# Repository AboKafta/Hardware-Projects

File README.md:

# Hardware Projects

My engineering work, split into personal projects and school projects, each in its own folder.

## Personal Projects

### PCB

| Project | Tool | Description |
|---|---|---|
| [RP2350 Dev Board](Personal/PCB/RP2350-Dev-Board) | KiCad | Custom development board for the RP2350 microcontroller, with bring-up and GPIO test firmware |
| [Room Temperature Monitor](Personal/PCB/Room-Temperature-Monitor) | Altium | Room temperature monitor on a custom PCB built around an Arduino Nano |
| [Piano](Personal/PCB/Piano) | KiCad | Arduino Nano-based piano board with a piezo speaker |
| [Blinking Heart](Personal/PCB/BlinkingHeart) | KiCad | Battery-powered blinking LED heart board |

### Embedded

| Project | Tool | Description |
|---|---|---|
| [MP3 Player](Personal/Embedded/MP3-Player) | Arduino | MP3 player firmware with a wiring diagram |
| [Prosthetic Hand](Personal/Embedded/ProstheticHand) (unfinished) | Arduino | Prototype firmware driving motors from sensor input |

## School Projects

| Project | Course | Tools | Description |
|---|---|---|---|
| [Escape Room Watch](School/Escape-Room-Watch) | Cornerstone of Engineering 2 | Arduino, SolidWorks | Team project: a space-themed escape room puzzle. An Arduino Nano plays three songs on a buzzer, and guessing all three with the buttons shows a lock code on an OLED. I built the electronics and wrote the firmware; my teammates designed and 3D-printed the watch and transmitter (models in `CAD`) |
| [Frog Launcher](School/Frog-Launcher) | Cornerstone of Engineering 1 | MicroPython | Team project: an arcade machine where players launch frogs onto lily pads worth 1 to 3 points and avoid alligators worth -1. I wrote all the code for the Raspberry Pi Pico, built the LCD scoreboard, and rewired the circuit |
| [Chessboard](School/Chessboard) | Cornerstone of Engineering 2 | SolidWorks | Kingdom Hearts-themed chess set: the board and every piece modeled as parts and an assembly, with a final report |
| [Secrets of the Phoenicians](School/Secrets-of-the-Phoenicians) | Cornerstone of Engineering 2 | MATLAB App Designer | Puzzle adventure game set in ancient Phoenicia, using switches, a dropdown, and buttons, with three endings |
| [RPG Fighting Game](School/RPG-Fighting-Game) | Cornerstone of Engineering 1 | Python | Turn-based boss fight with attack, capture, and befriend options, built around a class |
| [Classic Circuit Calculator](https://github.com/brodienewhouse/Classic-Circuit-Calculator) (in progress) | Computing Fundamentals for Engineers | C++ | Team project: calculates current, resistance, voltage, and power for simple series and parallel resistor circuits, with a touch-display frontend. Hosted in a teammate's repo |

## Opening the files

- **KiCad:** open the `.kicad_pro` file in the project folder.
- **Altium:** open `TempMonitor.PrjPcb` in Altium Designer.
- **SolidWorks:** open the `.SLDASM` assembly file, keeping its part files in the same folder. Chessboard has a PDF report for viewing without SolidWorks.
- **Arduino:** open the `.ino` files in the Arduino IDE.
- **MicroPython:** open the `.py` files in Thonny and run them on a Raspberry Pi Pico.
- **Python:** run `RPGFightingGame.py` with Python 3.
- **MATLAB:** open `ML3FINAL.mlapp` in App Designer.

Where included, Gerber files for fabrication are in a `.zip` inside the project folder.

## AI assistance

Most of the firmware in this repo was developed with coding assistance from Claude, Anthropic's AI assistant.

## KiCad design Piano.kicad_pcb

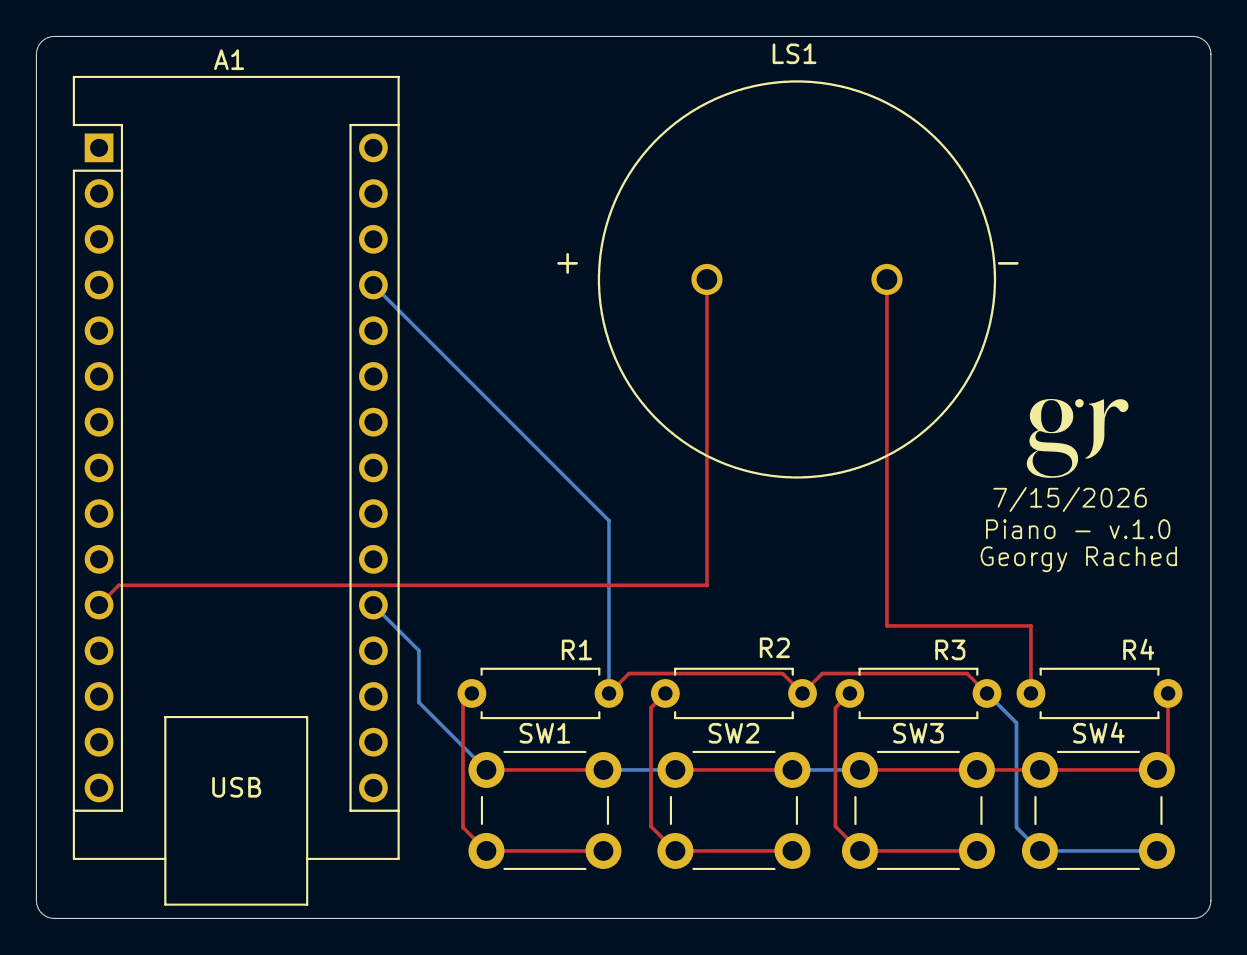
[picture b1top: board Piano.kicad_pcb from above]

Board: 2 copper layers, 65.2 x 49.0 mm, 10 parts (0 on the bottom side), 7 nets.

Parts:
A1: Arduino_Nano_Every; Arduino_Nano
LS1: PKM22EPPH4001-B0; piezo
R1: 220; R_Axial_DIN0207_L6.3mm_D2.5mm_P7.62mm_Horizontal
R2, R4: 10K; R_Axial_DIN0207_L6.3mm_D2.5mm_P7.62mm_Horizontal
R3: 1M; R_Axial_DIN0207_L6.3mm_D2.5mm_P7.62mm_Horizontal
SW1, SW2, SW3, SW4: SW_Push; SW_PUSH_6mm

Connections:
+5V: A1.27 (+5V), R1.1, R2.1, R3.1, SW4.2
/D8: A1.11 (D8), LS1.P
/INPUT: A1.20 (A1), R4.1, SW1.1, SW2.1, SW3.1, SW4.1
GND: A1.4 (GND), A1.29 (GND), LS1.N, R4.2
unnamed: R1.2, SW1.2
unnamed: R2.2, SW2.2
unnamed: R3.2, SW3.2
